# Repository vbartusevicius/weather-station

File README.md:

# AeroMet V1 — Solid-State Roof Weather & Air-Quality Station

Open-source rooftop weather and air-quality station with **no moving parts** (`Ø 96 × 235 mm`, UV-stabilised ASA):
ultrasonic wind, acoustic rain and hail, UV / sunlight / night-sky brightness, temperature, humidity, pressure, lightning,
PM1 / PM2.5 / PM10, VOC / NOx and true CO₂. It runs from `12–32 V DC`, talks Wi-Fi and RS-485, serves its own web
dashboard and appears in Home Assistant by itself.

<table>
  <tr>
    <td width="34%"></td>
    <td width="66%"></td>
  </tr>
</table>

[What it measures](#what-it-measures) · [Hardware](#hardware) · [Web UI](#web-ui) · [Build one](#build-one) ·
[Firmware](#firmware) · [Development](#development)

## What it measures

| Measurement | Sensor | Range |
| :--- | :--- | :--- |
| Wind speed & direction | 4× 40 kHz ultrasonic transducers, time of flight (STM32G431 crown) | 0–60 m/s, 0.1° |
| Rain & hail | 4 piezo discs under the lid, acoustic impacts | 0–200 mm/h, hail size |
| UV index, UV-A / UV-B, sunlight, night sky | GUVB-C21SD + GUVA-C22SD photodiodes + TSL25911 under a PTFE dome | UVI 0–16+, 0.0002–88 000 lx |
| Temperature & humidity | Sensirion SHT40 in a 5-plate radiation shield | ±0.2 °C, ±1.8 % RH |
| Pressure & thunder | Bosch BMP585 | ±0.06 hPa |
| Particulates | Plantower PMSA003I | PM1 / PM2.5 / PM10 |
| VOC & NOx | Sensirion SGP41 + Gas Index Algorithm | index 1–500 |
| CO₂ | Sensirion SCD41 (heated below −8 °C) | 400–5000 ppm |
| Lightning | AS3935 + 500 kHz ferrite antenna | 1–40 km |
| Compass, tilt, vibration | MMC5603 + LSM6DS3 | heading, mast tilt, ground vibration |

Full sensor, enclosure and board reference: **[docs/hardware.md](docs/hardware.md)**.

## Hardware

| Cutaway | Exploded | Six boards on one breakaway panel |
| :---: | :---: | :---: |
|  |  |  |
| radiation shield, probe cartridge, base bay | 13 printed parts, bayonet and threaded joints | crown, main, probe, power, dome, reflector (4-layer, 140.6 × 63.2 mm) |

<details>
<summary><b>More renders</b>: inside view, every printed part, board plots</summary>

| Inside | Base | Pagoda | Wind tunnel |
| :---: | :---: | :---: | :---: |
|  |  |  |  |
| **Crown base** | **Crown lid** | **Struts** | **Probe sleeve** |
|  |  |  |  |

Board plots (top / bottom SVG): [crown](hardware/releases/v1/crown/renders/top.svg) ·
[main](hardware/releases/v1/main/renders/top.svg) · [probe](hardware/releases/v1/probe/renders/top.svg) ·
[power](hardware/releases/v1/power/renders/top.svg) · [dome](hardware/releases/v1/dome/renders/top.svg) ·
[reflector](hardware/releases/v1/reflector/renders/top.svg) · [panel](hardware/releases/v1/panel/renders/top.svg)

</details>

## Web UI

The station serves its dashboard over Wi-Fi (no cloud, no app). Every value is computed by the firmware; the page only
displays it.

| Now | Trends |
| :---: | :---: |
|  |  |
| live readings, forecast, sun & moon, air quality, lightning | any metrics from 1 hour to 6 months, wind rose, records, CSV export |
| **Calibration** | **Setup** |
|  |  |
| station health, home calibration with household items | Wi-Fi, MQTT / Home Assistant, RS-485 monitor, firmware update |

Also: MQTT with Home Assistant auto-discovery, and an RS-485 poll / response protocol (CRC-16 frames with every
sensor) for wired loggers.

## Build one

1. **Order the boards** with assembly: ODB++ for AISLER, Gerbers + MPN BOM + CPL for PCBWay / Eurocircuits, or the
   JLCPCB files for the breakaway panel ([`hardware/releases/v1/`](hardware/releases/v1/); which file goes where:
   [docs/building.md](docs/building.md#3-ordering-the-pcbs-and-assembly)).
2. **Print the enclosure**: 8 print plates in [`enclosure/print/`](hardware/releases/v1/enclosure/print/) (MJF / SLS
   nylon or ASA), plus standard O-rings and a turned PTFE dome.
3. **Assemble and seal**: harnesses, conformal coating and sealing in **[docs/building.md](docs/building.md)**.
4. **Flash** the station once over USB, then **bring it up and calibrate** it at home:
   **[CALIBRATION.md](CALIBRATION.md)**.

Open design questions and acceptance checks: [REVIEW_CHECKLIST.md](REVIEW_CHECKLIST.md).

## Firmware

Download from **[Releases](https://github.com/vbartusevicius/weather-station/releases)**: each release carries the
firmware and the complete hardware package (`aeromet-hardware-v1.zip`: Gerbers, BOM, CPL, STL / STEP print plates,
drawings, build and calibration guides). Every commit to `main` that passes CI is released, named after its UTC commit
time (`2026.10.24.0040`); the firmware reports the same version.

| File | Use |
| :--- | :--- |
| `usb-flash-firmware.bin` | first flash of a new board over USB: `esptool.py --chip esp32c6 write_flash 0x0 usb-flash-firmware.bin` |
| `firmware.bin` | later updates from the Web UI (Setup → Firmware update); carries the crown firmware too |

The version is the UTC commit time, `yyyy.mm.dd.hhmm`. Local build: `python3 station/scripts/release_firmware.py`
→ `station/build/firmware/`.

## Development

| Folder | Contents |
| :--- | :--- |
| [`hardware/`](hardware/) | spec (`product/spec.yaml`), SKiDL circuits, KiCad layouts, simulations, release package |
| [`mechanical/`](mechanical/) | CadQuery enclosure generator and renderer |
| [`station/`](station/) | ESP32-C6 firmware (ESP-IDF), Web UI (`station/data/`), simulator, unit and Web UI tests |
| [`crown/`](crown/) | STM32G431 crown firmware (ultrasonic wind, rain, lightning) |

```bash
python3 hardware/scripts/build.py                     # everything: hardware, CAD, release, firmware, tests
docker compose --profile lint run --rm -T cpp-lint "pio test -d station -e native"   # firmware unit tests
python3 station/scripts/mock_webui_server.py          # Web UI on the simulator: http://127.0.0.1:8765
docker compose --profile lint run --rm lint check .   # lint
python3 docs/render_readme_images.py                  # refresh the README screenshots and PCB render
```

Architecture, conventions and every command: [AGENTS.md](AGENTS.md).

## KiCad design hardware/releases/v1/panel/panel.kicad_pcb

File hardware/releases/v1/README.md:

# AeroMet V1 Hardware Release Package (6 Boards on 1 Breakaway Panel + 13-Part Enclosure)

Generated by `python3 hardware/scripts/build.py` (`release.py`) from `hardware/layout/v1/` and `mechanical/`: per-board
KiCad DRC reports (`<board>/drc.json`), ODB++ (AISLER; also PCBWay / Eurocircuits), Gerber X2 + drills + IPC-D-356
netlist, a generic MPN BOM and placement file (PCBWay, Eurocircuits), JLCPCB BOM / CPL, hand-fit lists,
STEP models and renders; every JLCPCB SMT part verified pin-for-pin against its EasyEDA footprint. Which file goes to
which fab house: [`docs/building.md`](../../../docs/building.md#3-ordering-the-pcbs-and-assembly). Design status and open prototype checks:
[`REVIEW_CHECKLIST.md`](../../../REVIEW_CHECKLIST.md); commissioning: [`CALIBRATION.md`](../../../CALIBRATION.md).

| Board | Size | Layers | Thickness | Role in the Station | Folder |
| :--- | :---: | :---: | :---: | :--- | :---: |
| **Breakaway Panel (`panel`)** | **`140.6 × 63.2 mm`** | **4** | **`1.6 mm`** | **All six boards on one PCB (column packing, tabs clear of parts; order with "edge rails / fiducials added by JLCPCB"), double-sided assembly** | **`panel/`** |
| **1. `main`** | `32.0 × 52.0 mm` | 4 | `1.6 mm` | Right half of the base bay: 4-pole terminal `J1` (`12–32 V` + `RS-485 A/B`), `1.1 A` / `60 V` PTC, `SMAJ36A` TVS, `SS16` reverse-polarity diode, socketed `XIAO ESP32-C6` behind an `LM66100`, `SP3485EN` RS-485 (separate TX / RX / DE, `390 Ω` fail-safe bias, `PSM712` TVS, optional `120 Ω` `R26`), `LSM6DS3TR-C` IMU, `ADS1115` heater monitor, `AO3400A` reflector heater switch, crown control lines. Power nets `0.4 mm`. | `main/` |
| **2. `crown`** | `60 × 60 mm` (notched) | 4 | `1.6 mm` | `STM32G431RBT6` (I²C peripheral `0x2A`): 4× `UCC27524` H-bridge transducer drivers on `+12V_HEAT` with `BAV99` T/R isolation, `74HC4052` + `TLV9062` receive chain into the OPAMP1 PGA biased at VREF (PA3), piezo charge amplifier (22k / 1 nF anti-alias), `AS3935` + `MA5532-AE` on SPI1, `MMC5603NJ` compass, `XC6206` LDO, dome socket `J10`, spare `+12V_HEAT` `J11`, SWD footprint `J12`. | `crown/` |
| **3. `reflector`** | `24.0 × 24.0 mm` | 4 | `1.6 mm` | De-icing heater under the reflector cone: 4× `120 Ω` `2512` `2 W` in parallel on `+12V_HEAT` (`30 Ω`, `4.5 W` regulated), `10k` NTC `TH1`, 4-pin SMD male header `J1` to probe `J2`. | `reflector/` |
| **4. `dome`** | `Ø 15.6 mm` round | 4 | `1.6 mm` | UV / visible / NIR micro-PCB under the default flanged PTFE dome diffuser (lathe or CNC version; backup: the `Ø 20 × 2 mm` `JGS1` window in `crown_window`): `GUVB-C21SD` UV-B + `GUVA-C22SD` UV-A photodiodes, `TLV9062`, `ADS1115` (0x49), `TSL25911FN`, 4-pin B2B header `J1`. | `dome/` |
| `dome_legacy` | `Ø 13.6 mm` round | 4 | `1.6 mm` | Backup dome, same riser: `LTR-390UV-01` (discontinued), `TSL25911FN`, `GUVB-C31SM` (obsolete). Released separately (not on the panel, not in the order files). | `dome_legacy/` |
| **5. `probe`** | `14.0 × 56.0 mm` | 4 | `1.6 mm` | Vertical pagoda stem, bottom to top: `J1`, slot, `SHT40-AD1F-R2`, slot (no ground plane in its bridges), `SGP41-D-R4` + `BMP585`, `SCD41-D-R2` with the backside `0.42 W` heater and `LM2903` `−7.6 °C` thermostat, right-angle socket `J2` to the reflector. | `probe/` |
| **6. `power`** | `28.5 × 21.5 mm` | 4 | `1.6 mm` | Flat under `main`: 2× `TPS54360` (`743 kHz`) → `+5V` electronics and `+12V_HEAT` (heaters, transducer drive), `AP2112K-3.3` → `+3V3_PROBE`, 10-pin JST-SH `J1` to main `J5`. | `power/` |

Enclosure (`enclosure/`): assembled-position STL / STEP per part, `print/<plate>.stl` (8 print plates, the only files to
print), renders, and purchase drawings in `drawings/`: `ptfe_dome_lathe.svg` / `ptfe_dome_cnc.svg` (default UV / light cover:
flanged PTFE dome, lathe version from round rod or CNC hemisphere version; matching `ptfe_dome_<kind>.step` in the lathe frame for
the CNC quote) and `jgs1_window.svg` (backup window, `crown_window`
top).

Hand assembly: every board folder has `<board>_assembly.pdf`: one page per populated side (bottom mirrored, as seen
from below), every part with reference + value, a red dot on pin 1 (ICs, connectors, diodes), `[H]` on hand-fitted
parts, same value = same colour, large parts dashed (fit them last), and a value list with quantities and references.

Print process: the enclosure is designed for MJF / SLS PA12 (powder nylon, ~±0.3 mm), but **no part of it has been
printed yet** (no tested process). Design rules it follows (`mechanical/tests/test_print_rules.py`): snap beams ≤ 2.5 %
strain, hook undersides ≥ 0.3 mm above the board with a lead-in ramp, printed threads 0.30 mm flank clearance per side,
separate bodies on one plate ≥ 0.3 mm apart (reset button 0.40 mm), engraved marks ≥ 0.6 mm deep and ≥ 3 mm. Check on the
first print: clip snap force, thread fit (strut M12 + locknuts, probe sleeve M22, dome / window nuts M22), the three
bayonet joints locking, the reset button and umbrella moving freely, and the lock marks being readable.

## Parts orders for self-assembly (one complete station)

Generated by `hardware/scripts/order_parts.py` with every release (`release.py`); `hardware/tests/test_order_files.py`
fails when they differ from a fresh export. Live stock check: `python3 hardware/scripts/order_parts.py --check`.

| File | Upload to | Column mapping |
| :--- | :--- | :--- |
| `order_lcsc.csv` | lcsc.com → **BOM Tool** → Upload BOM | `LCSC Part Number` → *LCSC Part #*, `Quantity` → *Quantity*; optional `Manufacturer Part Number` → *MPN*, `Designators` → *Designator*, `Value` / `Footprint` → *Comment* / *Footprint*. Set the multiplier to 1 (one station); LCSC rounds each line up to its minimum order. |
| `order_elsewhere.csv` | by hand, per shop | electronics the LCSC store does not sell: `Mouser` / `Digi-Key` / `TME` columns (several numbers per shop separated by ` / `, the first preferred) + `Other sources`. General hardware (fasteners, O-rings, cable gland, thermal filler, coating, UV cover) and printed parts are only in `assembly_parts.csv` (column `Category`) |

`order_lcsc.csv` merges all boards (the legacy dome as `dome_legacy:ref`) into one line per LCSC number (designators `board:ref`) and adds the off-board
parts whose `Part` names an LCSC number. JLCPCB numbers the LCSC store does not stock are swapped for verified store
numbers in `hardware/product/lcsc_store.yaml` (the board BOMs keep the JLCPCB numbers). Parts the LCSC store does not sell (Sensirion SCD41 / SGP41 / SHT40, AS3935) are listed in
`order_elsewhere.csv` with a verified distributor (TME / Farnell / RS) from the `elsewhere:` section of that file. Run `--check` before ordering:
store stock changes daily, and the check lists every line that cannot be ordered as it stands.

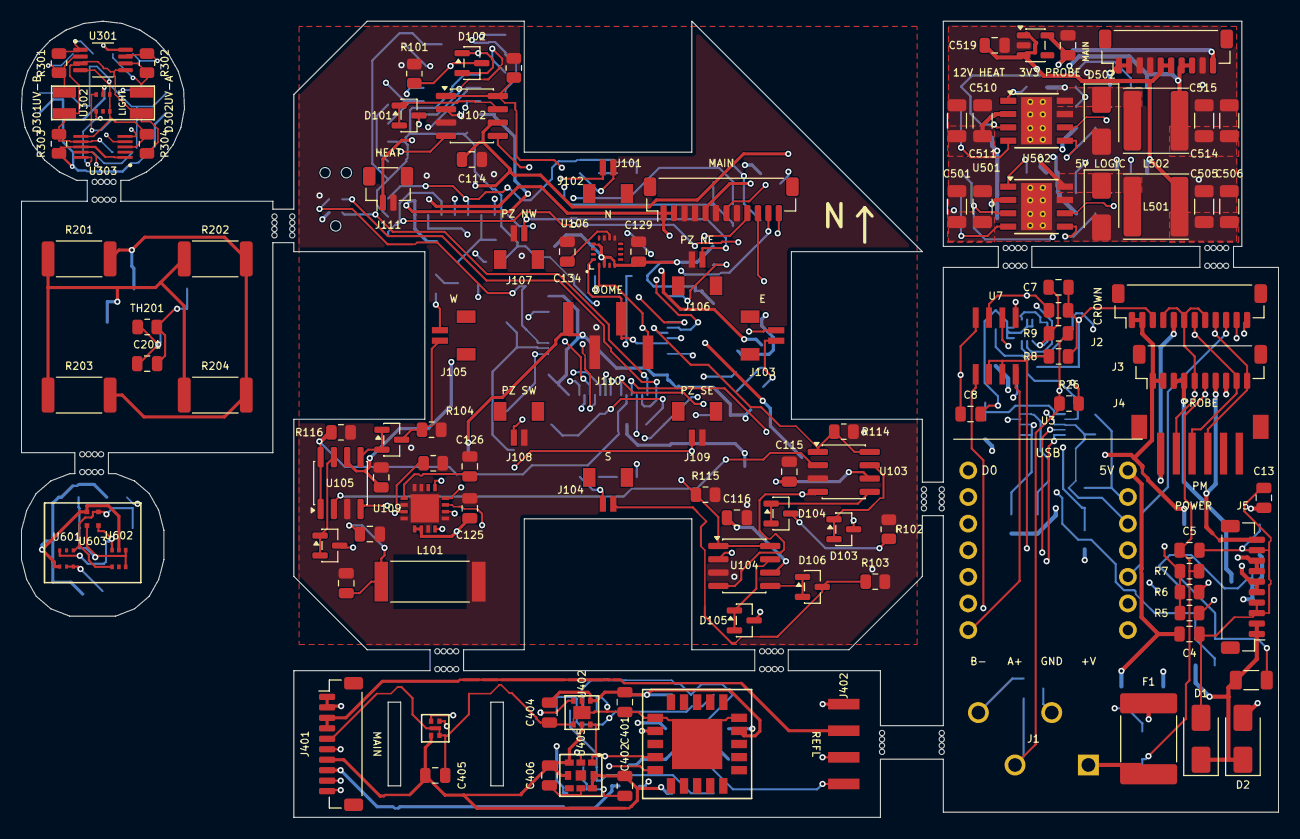
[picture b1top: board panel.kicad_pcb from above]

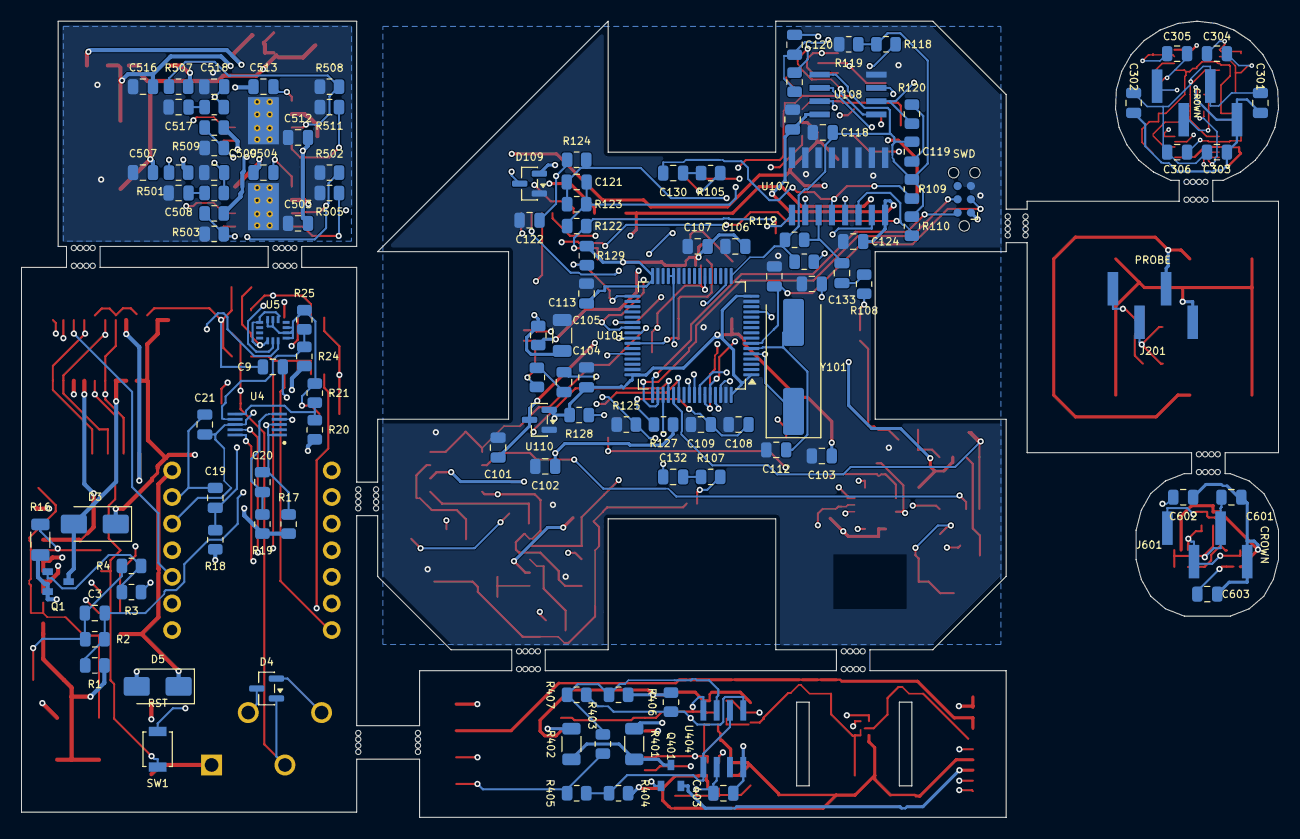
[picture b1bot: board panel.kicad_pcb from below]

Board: 4 copper layers, 120.0 x 76.0 mm, 236 parts (120 on the bottom side), 144 nets.

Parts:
C1, C501, C502, C510, C511: 2u2 100V; C_1206_3216Metric
C3, C5, C7, C8, C9, C21, C103, C104, C105, C106, C109, C110, C119, C123, C124, C129, C201, C301, C302, C303, C402, C403, C404, C405, C406, C504, C507, C513, C516, C601, C602: 100n 50V; C_0805_2012Metric
C4, C13, C102, C107, C134, C401, C520: 10u 10V; C_0805_2012Metric
C19, C20, C101, C108, C114, C115, C116, C117, C118, C125, C126, C306, C519, C603: 1u 50V; C_0805_2012Metric
C111, C112: 33p C0G 50V; C_0805_2012Metric
C113, C514, C515: 22u 25V; C_1206_3216Metric
C120: 220p C0G 50V; C_0805_2012Metric
C121, C305: 22n 50V; C_0805_2012Metric
C122: 1n 50V; C_0805_2012Metric
C127, C128: 470p C0G 50V; C_0805_2012Metric
C130, C131, C132, C133, C304: 10n 50V; C_0805_2012Metric
C503, C512: 100n 100V; C_0805_2012Metric
C505, C506: 47u 10V; C_1206_3216Metric
C508: 33n 50V; C_0805_2012Metric
C509, C518: 68p C0G 50V; C_0805_2012Metric
C517: 18n 50V; C_0805_2012Metric
D1: SMAJ36A; D_SMA
D2, D3: SS16; D_SMA
D4: PSM712; SOT-23
D5: SS14; D_SMA
D101, D102, D103, D104, D105, D106, D107, D108, D109: BAV99; SOT-23
D301: GUVB-C21SD; Genicom_COB2418
D302: GUVA-C22SD; Genicom_COB2418
D501, D502: B360A; D_SMA
F1: 1.1A; Fuse_2920_7451Metric
J1: 12-32V + RS485; TerminalBlock_Kefa_KF250-3.5-4P
J2: Crown board; JST_SH_BM12B-SRSS-TB_1x12-1MP_P1.00mm_Vertical
J3: Probe board; JST_SH_BM10B-SRSS-TB_1x10-1MP_P1.00mm_Vertical
J4: PMSA003I PM; JST_B6B-ZR-SM4-TF
J5: Power board; JST_SH_BM10B-SRSS-TB_1x10-1MP_P1.00mm_Vertical
J101: Main board; JST_SH_BM12B-SRSS-TB_1x12-1MP_P1.00mm_Vertical
J102: XD_N; JST_BM02B-SRSS-TB
J103: XD_E; JST_BM02B-SRSS-TB
J104: XD_S; JST_BM02B-SRSS-TB
J105: XD_W; JST_BM02B-SRSS-TB
J106: PIEZO_NE; JST_BM02B-SRSS-TB
J107: PIEZO_NW; JST_BM02B-SRSS-TB
J108: PIEZO_SW; JST_BM02B-SRSS-TB
J109: PIEZO_SE; JST_BM02B-SRSS-TB
J110: DOME_SOCKET; HX_PZ2.54-1x4P-SMD
J111: AUX 12V_HEAT; JST_SH_BM02B-SRSS-TB_1x02-1MP_P1.00mm_Vertical
J112: SWD; Tag-Connect_TC2030-IDC-NL_2x03_P1.27mm_Vertical
J201: Probe T-Header SMD; HX_PZ2.54-1x4P-SMD
J301, J601: CROWN_RISER; HX_PZ2.54-1x4P-SMD
J401, J501: Main board; JST_SH_BM10B-SRSS-TB_1x10-1MP_P1.00mm_Vertical
J402: Reflector T-Socket SMD; HX_PM2.54-1x4P-RA-SMD
L101: 100uH; AS3935_Antenna_MA5532_SDTR1103
L501: 8.2uH; L_Sunlord_SWPA6045S
L502: 22uH; L_Sunlord_SWPA6045S
MOUSE_BITES: DNP
Q1, Q401: AO3400A; AOS_AO3400A_SOT-23
R1, R4, R303: 100k; R_0805_2012Metric
R2, R7, R8, R21, R24, R25, R118, R119, R125, R126, R128, R129, R304, R403, R404, R406, R510: 10k; R_0805_2012Metric
R3, R101, R102, R103, R104: 330R; R_0805_2012Metric
R5, R6: 2k2; R_0805_2012Metric
R9, R10: 390R; R_0805_2012Metric
R16: 0R1; R_1206_3216Metric
R17: 1R; R_0805_2012Metric
R18, R19, R120, R122: 1k; R_0805_2012Metric
R20: 30k; R_0805_2012Metric
R26: 120R; R_0805_2012Metric
R105, R106, R107, R108: 47k; R_0805_2012Metric
R109, R110, R111, R112: 1M; R_0805_2012Metric
R113, R114, R115, R116: 4k7; R_0805_2012Metric
R117, R127: 10R; R_0805_2012Metric
R121: 6k8; R_0805_2012Metric
R123, R302: 4M7; R_0805_2012Metric
R124: 22k; R_0805_2012Metric
R201, R202, R203, R204: 120R; R_2512_6332Metric
R301: 10M; R_0805_2012Metric
R401, R402: 680R; R_1206_3216Metric
R405: 51k; R_0805_2012Metric
R407: 470k; R_0805_2012Metric
R501, R507: 511k; R_0805_2012Metric
R502, R508: 82k5; R_0805_2012Metric
R503: 53k6; R_0805_2012Metric
R504: 10k2; R_0805_2012Metric
R505, R511: 130k; R_0805_2012Metric
R506, R512: 6k49; R_0805_2012Metric
R509: 140k; R_0805_2012Metric
SW1: SERVICE; SW_SPST_B3U-1000P
TH201, TH401: 10k NTC; R_0805_2012Metric
U3: XIAO ESP32C6; XIAO_ESP32C6_Header
U4, U303: ADS1115IDGSR; TI_ADS1115_VSSOP-10
U5: LSM6DS3TR-C; ST_LSM6DS3TR-C_LGA-14
U7: SP3485EN-L/TR; ON_LM393DR2G_SOIC-8
U101: STM32G431RBT6; LQFP-64_10x10mm_P0.5mm
U102, U103, U104, U105: UCC27524ADR; SOIC-8_3.9x4.9mm_P1.27mm
U106: MMC5983MA; MEMSIC_MMC5983MA_LGA-16
U107: 74HC4052D; TI_CD4052BM96_SOIC-16
U108: TLV9062IDR; TI_TLV9062IDR_SOIC-8
U109: AS3935-BQFT; ScioSense_AS3935_QFN-16
U110: XC6206P332MR; SOT-23
U301: TLV9062IDGKR; TI_TLV9062_VSSOP-8
U302, U602: TSL25911FN; AMS_TSL25911FN
U401: SCD41-D-R2; Sensirion_SCD41_LGA-20
U402: SGP41-D-R4; Sensirion_SGP41_DFN-6
U403: SHT40-AD1F-R2; Sensirion_SHT45_DFN-4
U404: LM2903DR2G; ON_LM393DR2G_SOIC-8
U405: BMP585; Bosch_BMP585_LGA-9
U501, U502: TPS54360DDAR; TI_SO-PowerPAD-8_ThermalVias
U503: AP2112K-3.3; SOT-23-5
U601: LTR-390UV-01; LiteOn_LTR-390UV-01
U603: GUVB-C31SM; GenUV_GUVB-C31SM
Y101: 8MHz; Crystal_SMD_HC49-SD

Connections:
+3V3: C7.1, C8.1, C9.1, C21.1, R5.1, R6.1, R7.1, R9.1, U3.12, U4.8, U5.5, U5.8, U5.12, U7.8
+3V3_PROBE: J3.7, J5.10
+5V: C13.1, D5.2, J2.5, J4.1, J5.5, J5.6, R24.1
+5V_XIAO: C4.1, D5.1, U3.14
+12V_HEAT: D3.1, J2.1, J2.2, J3.1, J3.2, J5.7, J5.8, R20.1
CO2_HEAT_RTN: J3.8, R17.1, R19.1
CROWN_+3V3: C102.1, C103.1, C104.1, C105.1, C106.1, C107.1, C123.1, C124.1, C125.1, C129.1, D109.2, J110.1, J112.1, R127.1, R128.2, R129.2, U101.1, U101.16, U101.32, U101.48, U101.64, U106.2, U106.4, U106.13, U107.16, U108.8, U109.5, U109.6, U110.2
CROWN_+3V3A: C108.1, C109.1, R118.1, R127.2, U101.28, U101.29
CROWN_+5V: C101.1, J101.5, U110.3
CROWN_+12V_HEAT: J101.1, J101.2, J111.1, R117.1
CROWN_AS_ACG: C126.1, U109.1
CROWN_AS_CS: U101.51, U109.8
CROWN_AS_INP: C127.1, C128.1, L101.1, R126.1, U109.3
CROWN_AS_IRQ: U101.62, U109.10
CROWN_AS_MISO: U101.57, U109.12
CROWN_AS_MOSI: U101.58, U109.13
CROWN_AS_SCK: U101.56, U109.11
CROWN_BL_PA10: R128.1, U101.44
CROWN_BL_PB12: R129.1, U101.33
CROWN_BOOT0: J2.12, U3.3
CROWN_CROWN_BOOT0: J101.12, R125.1, U101.61
CROWN_CROWN_IRQ: J101.10, U101.54
CROWN_CROWN_NRST: C110.1, J101.11, J112.3, U101.7
CROWN_GND: C101.2, C102.2, C103.2, C104.2, C105.2, C106.2, C107.2, C108.2, C109.2, C110.2, C111.2, C112.2, C113.2, C114.2, C115.2, C116.2, C117.2, C118.2, C122.2, C123.2, C124.2, C125.2, C126.2, C127.2, C128.2, C129.2, C134.2, D109.1, J101.3, J101.4, J101.6, J101.8, J106.2, J107.2, J108.2, J109.2, J110.2, J111.2, J112.5, L101.2, R101.2, R102.2, R103.2, R104.2, R113.2, R114.2, R115.2, R116.2, R119.2, R125.2, R126.2, U101.15, U101.27, U101.31, U101.47, U101.63, U102.3, U103.3, U104.3, U105.3, U106.9, U106.11, U107.1, U107.2, U107.3, U107.4, U107.5, U107.6, U107.7, U107.8, U108.4, U109.2, U109.4, U109.7, U109.9, U109.15, U109.16, U109.17, U110.1
CROWN_I2C_SCL: J101.9, J110.4, U101.22, U106.1
CROWN_I2C_SDA: J101.7, J110.3, U101.42, U106.16
CROWN_IRQ: J2.10, U3.10
CROWN_MAG_CAP: C134.1, U106.10
CROWN_MUX_S0: U101.59, U107.10
CROWN_MUX_S1: U101.60, U107.9
CROWN_NRST: J2.11, U3.11
CROWN_PIEZO_IN: D109.3, J106.1, J107.1, J108.1, J109.1, R122.1
CROWN_PIEZO_INV: C121.1, R122.2, R123.1, U108.6
CROWN_PIEZO_OUT: C121.2, R123.2, R124.1, U108.7
CROWN_RAIN_ADC: C122.1, R124.2, U101.18
CROWN_SWCLK: J112.4, U101.50
CROWN_SWDIO: J112.2, U101.49
CROWN_TX_N: U101.52, U102.4, U103.4, U104.4, U105.4
CROWN_TX_P: U101.38, U102.2, U103.2, U104.2, U105.2
CROWN_US_AMP_FB: C120.1, R120.1, R121.1, U108.2
CROWN_US_AMP_G: C119.1, R120.2
CROWN_US_AMP_OUT: C120.2, R121.2, U101.13, U108.1
CROWN_US_RX_MUX: U107.13, U108.3
CROWN_US_VREF: C118.1, C119.2, R109.2, R110.2, R111.2, R112.2, R118.2, R119.1, U101.17, U108.5
CROWN_VDRV: C113.1, C114.1, C115.1, C116.1, C117.1, R117.2, U102.6, U103.6, U104.6, U105.6
CROWN_XD_EN_E: R114.1, U101.40, U103.1, U103.8
CROWN_XD_EN_N: R113.1, U101.39, U102.1, U102.8
CROWN_XD_EN_S: R115.1, U101.41, U104.1, U104.8
CROWN_XD_EN_W: R116.1, U101.53, U105.1, U105.8
CROWN_XD_E_A: D103.3, J103.1, R106.1
CROWN_XD_E_B: D104.3, J103.2, R102.1
CROWN_XD_E_OUT_A: D103.1, D103.2, U103.7
CROWN_XD_E_OUT_B: D104.1, D104.2, U103.5
CROWN_XD_E_RX: C131.2, R110.1, U107.14
CROWN_XD_E_RXC: C131.1, R106.2
CROWN_XD_N_A: D101.3, J102.1, R105.1
CROWN_XD_N_B: D102.3, J102.2, R101.1
CROWN_XD_N_OUT_A: D101.1, D101.2, U102.7
CROWN_XD_N_OUT_B: D102.1, D102.2, U102.5
CROWN_XD_N_RX: C130.2, R109.1, U107.12
CROWN_XD_N_RXC: C130.1, R105.2
CROWN_XD_S_A: D105.3, J104.1, R107.1
CROWN_XD_S_B: D106.3, J104.2, R103.1
CROWN_XD_S_OUT_A: D105.1, D105.2, U104.7
CROWN_XD_S_OUT_B: D106.1, D106.2, U104.5
CROWN_XD_S_RX: C132.2, R111.1, U107.15
CROWN_XD_S_RXC: C132.1, R107.2
CROWN_XD_W_A: D107.3, J105.1, R108.1
CROWN_XD_W_B: D108.3, J105.2, R104.1
CROWN_XD_W_OUT_A: D107.1, D107.2, U105.7
CROWN_XD_W_OUT_B: D108.1, D108.2, U105.5
CROWN_XD_W_RX: C133.2, R112.1, U107.11
CROWN_XD_W_RXC: C133.1, R108.2
CROWN_XTAL_IN: C111.1, U101.5, Y101.1
CROWN_XTAL_OUT: C112.1, U101.6, Y101.2
DOME_+3V3: C301.1, C302.1, C303.1, J301.1, R303.1, U301.8, U302.5, U303.1, U303.8
DOME_GND: C301.2, C302.2, C303.2, C306.2, J301.2, R304.2, U301.4, U302.3, U302.4, U303.3, U303.6
DOME_I2C_SCL: J301.4, U302.1, U303.10
DOME_I2C_SDA: J301.3, U302.6, U303.9
DOME_LEGACY_+3V3: C601.1, C602.1, C603.1, J601.1, U601.1, U602.5, U603.4
DOME_LEGACY_GND: C601.2, C602.2, C603.2, J601.2, U601.2, U601.3, U602.3, U602.4, U603.1
DOME_LEGACY_I2C_SCL: J601.4, U601.4, U602.1, U603.3
DOME_LEGACY_I2C_SDA: J601.3, U601.6, U602.6, U603.2
DOME_UVA_IN: C305.1, D302.2, R302.1, U301.6
DOME_UVA_OUT: C305.2, R302.2, U301.7, U303.5
DOME_UVB_IN: C304.1, D301.2, R301.1, U301.2
DOME_UVB_OUT: C304.2, R301.2, U301.1, U303.4
DOME_UV_VB: C306.1, D301.1, D302.1, R303.2, R304.1, U301.3, U301.5, U303.7
GND: C1.2, C3.2, C4.2, C5.2, C7.2, C8.2, C9.2, C13.2, C19.2, C20.2, C21.2, D1.2, D4.3, J1.2, J2.3, J2.4, J2.6, J2.8, J3.5, J4.2, J5.3, J5.4, J5.9, R2.2, R4.2, R8.2, R10.2, R16.2, R17.2, R21.2, R25.2, SW1.2, U3.13, U4.1, U4.3, U5.1, U5.2, U5.3, U5.6, U5.7, U7.5
HEAT_GATE: Q1.1, R3.2, R4.1
HEAT_PWM: R3.1, U3.4
HEAT_SENSE: Q1.2, R16.1, R18.1
HEAT_SW: D3.2, J3.3, J3.4, Q1.3
I2C_SCL: J2.9, J3.10, J4.4, R6.2, U3.6, U4.10, U5.13
I2C_SDA: J2.7, J3.9, J4.3, R5.2, U3.5, U4.9, U5.14
MON_5V: R20.2, R21.1, U4.6
MON_5V_LOGIC: R24.2, R25.1, U4.7
MON_PROBE: C20.1, R19.2, U4.5
MON_REFL: C19.1, R18.2, U4.4
NTC_SENSE: C5.1, J3.6, R7.2, SW1.1, U3.2
POWER_+3V3_PROBE: C520.1, J501.10, U503.5
POWER_+5V: C505.1, C506.1, C507.1, C519.1, J501.5, J501.6, L501.2, R503.1, U503.1, U503.3
POWER_+12V_HEAT: C514.1, C515.1, C516.1, J501.7, J501.8, L502.2, R509.1
POWER_GND: C501.2, C502.2, C503.2, C505.2, C506.2, C507.2, C508.2, C509.2, C510.2, C511.2, C512.2, C514.2, C515.2, C516.2, C517.2, C518.2, C519.2, C520.2, D501.2, D502.2, J501.3, J501.4, J501.9, R502.2, R504.2, R505.2, R508.2, R510.2, R511.2, U501.7, U501.9, U502.7, U502.9, U503.2
POWER_HEAT_BST: C513.1, U502.1
POWER_HEAT_CC: C517.1, R512.2
POWER_HEAT_COMP: C518.1, R512.1, U502.6
POWER_HEAT_EN: R507.2, R508.1, U502.3
POWER_HEAT_FB: R509.2, R510.1, U502.5
POWER_HEAT_RT: R511.1, U502.4
POWER_HEAT_SW: C513.2, D502.1, L502.1, U502.8
POWER_LOGIC_BST: C504.1, U501.1
POWER_LOGIC_CC: C508.1, R506.2
POWER_LOGIC_COMP: C509.1, R506.1, U501.6
POWER_LOGIC_EN: R501.2, R502.1, U501.3
POWER_LOGIC_FB: R503.2, R504.1, U501.5
POWER_LOGIC_RT: R505.1, U501.4
POWER_LOGIC_SW: C504.2, D501.1, L501.1, U501.8
POWER_VIN_PROT: C501.1, C502.1, C503.1, C510.1, C511.1, C512.1, J501.1, J501.2, R501.1, R507.1, U501.2, U502.2
PROBE_+3V3_PROBE: C401.1, C402.1, C404.1, C405.1, C406.1, J401.7, R403.1, R404.1, R406.1, U401.7, U401.19, U402.1, U402.5, U403.3, U405.3, U405.4, U405.7, U405.8
PROBE_+12V_HEAT: C403.1, J401.1, J401.2, J402.1, R401.1, R402.1, U404.8
PROBE_CO2_GATE: Q401.1, R406.2, R407.1, U404.1
PROBE_CO2_HEAT_RTN: J401.8, Q401.2
PROBE_CO2_HEAT_SW: Q401.3, R401.2, R402.2
PROBE_CO2_NTC: R403.2, R407.2, TH401.1, U404.3
PROBE_CO2_VSET: R404.2, R405.1, U404.2, U404.5
PROBE_GND: C401.2, C402.2, C403.2, C404.2, C405.2, C406.2, J401.5, J402.4, R405.2, TH401.2, U401.6, U401.20, U401.21, U402.2, U402.4, U402.7, U403.4, U403.5, U404.4, U404.6, U405.6
PROBE_HEAT_SW: J401.3, J401.4, J402.2
PROBE_I2C_SCL: J401.10, U401.9, U402.6, U403.2, U405.1
PROBE_I2C_SDA: J401.9, U401.10, U402.3, U403.1, U405.2
PROBE_NTC_SENSE: J401.6, J402.3
REFLECTOR_+12V_HEAT: J201.1, R201.1, R202.1, R203.1, R204.1
REFLECTOR_GND: C201.2, J201.4, TH201.2
REFLECTOR_HEAT_SW: J201.2, R201.2, R202.2, R203.2, R204.2
REFLECTOR_NTC_SENSE: C201.1, J201.3, TH201.1
RS485_A: D4.1, J1.3, R9.2, R26.1, U7.6
RS485_B: D4.2, J1.4, R10.1, R26.2, U7.7
RS485_DE: R8.1, U3.9, U7.2, U7.3
RS485_RX: U3.8, U7.1
RS485_TX: U3.7, U7.4
VIN_ADC: C3.1, R1.2, R2.1, U3.1
VIN_FUSED: D2.2, F1.2
VIN_PROT: C1.1, D1.1, D2.1, J5.1, J5.2, R1.1
VIN_RAW: F1.1, J1.1

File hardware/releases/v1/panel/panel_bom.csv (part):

Line,Qty,Designators,Value,Package,Type,Manufacturer,MPN,LCSC,Assembly
1,5,"C1,C501,C502,C510,C511",2u2 100V,C_1206_3216Metric,SMD,Samsung,CL31B225KCHSNNE,C170101,machine
2,14,"C101,C108,C114,C115,C116,C117,C118,C125,C126,C19,C20,C306,C519,C603",1u 50V,C_0805_2012Metric,SMD,Samsung,CL21B105KBFNNNE,C28323,machine
3,7,"C102,C107,C13,C134,C4,C401,C520",10u 10V,C_0805_2012Metric,SMD,Samsung,CL21A106KPFNNNE,C17024,machine
4,31,"C103,C104,C105,C106,C109,C110,C119,C123,C124,C129,C201,C21,C3,C301,C302,C303,C402,C403,C404,C405,C406,C5,C504,C507,C513,C516,C601,C602,C7,C8,C9",100n 50V,C_0805_2012Metric,SMD,YAGEO,CC0805KRX7R9BB104,C49678,machine
5,2,"C111,C112",33p C0G 50V,C_0805_2012Metric,SMD,YAGEO,CC0805JRNPO9BN330,C107115,machine
6,3,"C113,C514,C515",22u 25V,C_1206_3216Metric,SMD,Samsung,CL31A226KAHNNNE,C12891,machine
7,1,C120,220p C0G 50V,C_0805_2012Metric,SMD,YAGEO,CC0805JRNPO9BN221,C107112,machine
8,2,"C121,C305",22n 50V,C_0805_2012Metric,SMD,YAGEO,CC0805KRX7R9BB223,C107147,machine
9,1,C122,1n 50V,C_0805_2012Metric,SMD,YAGEO,CC0805KRX7R9BB102,C94121,machine
10,2,"C127,C128",470p C0G 50V,C_0805_2012Metric,SMD,YAGEO,CC0805JRNPO9BN471,C62771,machine
11,5,"C130,C131,C132,C133,C304",10n 50V,C_0805_2012Metric,SMD,YAGEO,CC0805KRX7R9BB103,C83170,machine
12,2,"C503,C512",100n 100V,C_0805_2012Metric,SMD,YAGEO,CC0805KKX7R0BB104,C106243,machine
13,2,"C505,C506",47u 10V,C_1206_3216Metric,SMD,Samsung,CL31A476MPHNNNE,C96123,machine
14,1,C508,33n 50V,C_0805_2012Metric,SMD,YAGEO,CC0805KRX7R9BB333,C107150,machine
15,2,"C509,C518",68p C0G 50V,C_0805_2012Metric,SMD,YAGEO,CC0805JRNPO9BN680,C107120,machine
16,1,C517,18n 50V,C_0805_2012Metric,SMD,YAGEO,CC0805JRX7R9BB183,C520032,machine
17,1,D1,SMAJ36A,D_SMA,SMD,MDD,SMAJ36A,C113967,machine
18,9,"D101,D102,D103,D104,D105,D106,D107,D108,D109",BAV99,SOT-23,SMD,Nexperia,"BAV99,215",C2500,machine
19,2,"D2,D3",SS16,D_SMA,SMD,MDD,SS16,C2481,machine
20,1,D301,GUVB-C21SD,Genicom_COB2418,SMD,Genicom,GUVB-C21SD,,hand-fit (not stocked by JLCPCB)
21,1,D302,GUVA-C22SD,Genicom_COB2418,SMD,Genicom,GUVA-C22SD,,hand-fit (not stocked by JLCPCB)
22,1,D4,PSM712,SOT-23,SMD,Protek,PSM712-LF-T7,C32677,machine
23,1,D5,SS14,D_SMA,SMD,MDD,SS14,C2480,machine
24,2,"D501,D502",B360A,D_SMA,SMD,Diodes Inc,B360A-13-F,C94193,machine
25,1,F1,1.1A,Fuse_2920_7451Metric,SMD,Littelfuse,2920L110/60V,C49318488,machine
26,1,J1,12-32V + RS485,TerminalBlock_Kefa_KF250-3.5-4P,THT,Cixi Kefa Elec,KF250-3.5-4P-1,C475156,machine
27,1,J101,Main board,JST_SH_BM12B-SRSS-TB_1x12-1MP_P1.00mm_Vertical,SMD,JST,BM12B-SRSS-TB(LF)(SN),C160398,machine
28,1,J102,XD_N,JST_BM02B-SRSS-TB,SMD,JST,BM02B-SRSS-TB(LF)(SN),C160388,machine
29,1,J103,XD_E,JST_BM02B-SRSS-TB,SMD,JST,BM02B-SRSS-TB(LF)(SN),C160388,machine
30,1,J104,XD_S,JST_BM02B-SRSS-TB,SMD,JST,BM02B-SRSS-TB(LF)(SN),C160388,machine
31,1,J105,XD_W,JST_BM02B-SRSS-TB,SMD,JST,BM02B-SRSS-TB(LF)(SN),C160388,machine
32,1,J106,PIEZO_NE,JST_BM02B-SRSS-TB,SMD,JST,BM02B-SRSS-TB(LF)(SN),C160388,machine
33,1,J107,PIEZO_NW,JST_BM02B-SRSS-TB,SMD,JST,BM02B-SRSS-TB(LF)(SN),C160388,machine
34,1,J108,PIEZO_SW,JST_BM02B-SRSS-TB,SMD,JST,BM02B-SRSS-TB(LF)(SN),C160388,machine
35,1,J109,PIEZO_SE,JST_BM02B-SRSS-TB,SMD,JST,BM02B-SRSS-TB(LF)(SN),C160388,machine
36,1,J110,DOME_SOCKET,HX_PZ2.54-1x4P-SMD,SMD,HCTL,HX PM2.54-1x4P TP-YQ,C42379197,machine
37,1,J111,AUX 12V_HEAT,JST_SH_BM02B-SRSS-TB_1x02-1MP_P1.00mm_Vertical,SMD,JST,BM02B-SRSS-TB(LF)(SN),C160388,machine
38,1,J2,Crown board,JST_SH_BM12B-SRSS-TB_1x12-1MP_P1.00mm_Vertical,SMD,JST,BM12B-SRSS-TB(LF)(SN),C160398,machine
39,1,J201,Probe T-Header SMD,HX_PZ2.54-1x4P-SMD,SMD,HANBO,HX PZ2.54-1x4P TP-YQ,C41417361,machine
40,1,J3,Probe board,JST_SH_BM10B-SRSS-TB_1x10-1MP_P1.00mm_Vertical,SMD,JST,BM10B-SRSS-TB(LF)(SN),C160396,machine
41,2,"J301,J601",CROWN_RISER,HX_PZ2.54-1x4P-SMD,SMD,HCTL,HX PZ2.54-1x4P TP-YQ,C41417361,machine
42,1,J4,PMSA003I PM,JST_B6B-ZR-SM4-TF,SMD,JST,B6B-ZR-SM4-TF(LF)(SN),C471473,machine
43,2,"J401,J501",Main board,JST_SH_BM10B-SRSS-TB_1x10-1MP_P1.00mm_Vertical,SMD,JST,BM10B-SRSS-TB(LF)(SN),C160396,machine
44,1,J402,Reflector T-Socket SMD,HX_PM2.54-1x4P-RA-SMD,SMD,HANBO,HX PM2.54-1x4P WT,C46061768,machine
45,1,J5,Power board,JST_SH_BM10B-SRSS-TB_1x10-1MP_P1.00mm_Vertical,SMD,JST,BM10B-SRSS-TB(LF)(SN),C160396,machine
46,1,L101,100uH,AS3935_Antenna_MA5532_SDTR1103,SMD,Coilcraft,MA5532-AE,,hand-fit (not stocked by JLCPCB)
47,1,L501,8.2uH,L_Sunlord_SWPA6045S,SMD,APV,ANR6045T8R2M,C7427168,machine
48,1,L502,22uH,L_Sunlord_SWPA6045S,SMD,Bourns,SRN6045TA-220M,C2044314,machine
49,2,"Q1,Q401",AO3400A,AOS_AO3400A_SOT-23,SMD,Alpha & Omega Semicon,AO3400A,C20917,machine
50,3,"R1,R303,R4",100k,R_0805_2012Metric,SMD,UNI-ROYAL,0805W8F1003T5E,C149504,machine
51,2,"R10,R9",390R,R_0805_2012Metric,SMD,UNI-ROYAL,0805W8F3900T5E,C17655,machine
52,5,"R101,R102,R103,R104,R3",330R,R_0805_2012Metric,SMD,UNI-ROYAL,0805W8F3300T5E,C17630,machine
53,4,"R105,R106,R107,R108",47k,R_0805_2012Metric,SMD,UNI-ROYAL,0805W8F4702T5E,C17713,machine
54,4,"R109,R110,R111,R112",1M,R_0805_2012Metric,SMD,UNI-ROYAL,0805W8F1004T5E,C17514,machine
55,4,"R113,R114,R115,R116",4k7,R_0805_2012Metric,SMD,UNI-ROYAL,0805W8F4701T5E,C17673,machine
56,2,"R117,R127",10R,R_0805_2012Metric,SMD,UNI-ROYAL,0805W8F100JT5E,C17415,machine
57,17,"R118,R119,R125,R126,R128,R129,R2,R21,R24,R25,R304,R403,R404,R406,R510,R7,R8",10k,R_0805_2012Metric,SMD,UNI-ROYAL,0805W8F1002T5E,C17414,machine
58,4,"R120,R122,R18,R19",1k,R_0805_2012Metric,SMD,UNI-ROYAL,0805W8F1001T5E,C17513,machine
59,1,R121,6k8,R_0805_2012Metric,SMD,UNI-ROYAL,0805W8F6801T5E,C17772,machine
60,2,"R123,R302",4M7,R_0805_2012Metric,SMD,UNI-ROYAL,0805W8F4704T5E,C17674,machine
61,1,R124,22k,R_0805_2012Metric,SMD,UNI-ROYAL,0805W8F2202T5E,C17560,machine
62,1,R16,0R1,R_1206_3216Metric,SMD,UNI-ROYAL,1206W4F100LT5E,C25334,machine
63,1,R17,1R,R_0805_2012Metric,SMD,UNI-ROYAL,0805W8F100KT5E,C25271,machine
64,1,R20,30k,R_0805_2012Metric,SMD,UNI-ROYAL,0805W8F3002T5E,C17621,machine
65,4,"R201,R202,R203,R204",120R,R_2512_6332Metric,SMD,YAGEO,RC2512FK-7W120RL,C7276687,machine
66,1,R26,120R,R_0805_2012Metric,SMD,UNI-ROYAL,0805W8F1200T5E,C17437,hand-fit (not stocked by JLCPCB)
67,1,R301,10M,R_0805_2012Metric,SMD,UNI-ROYAL,0805W8F1005T5E,C26108,machine
68,2,"R401,R402",680R,R_1206_3216Metric,SMD,FOJAN,FRP1206F6800TS,C48533685,machine
69,1,R405,51k,R_0805_2012Metric,SMD,UNI-ROYAL,0805W8F5102T5E,C17737,machine
70,1,R407,470k,R_0805_2012Metric,SMD,UNI-ROYAL,0805W8F4703T5E,C17709,machine
71,2,"R5,R6",2k2,R_0805_2012Metric,SMD,UNI-ROYAL,0805W8F2201T5E,C17520,machine
72,2,"R501,R507",511k,R_0805_2012Metric,SMD,UNI-ROYAL,0805W8F5113T5E,C17735,machine
73,2,"R502,R508",82k5,R_0805_2012Metric,SMD,YAGEO,RC0805FR-0782K5L,C276314,machine
74,1,R503,53k6,R_0805_2012Metric,SMD,UNI-ROYAL,0805W8F5362T5E,C21398,machine
75,1,R504,10k2,R_0805_2012Metric,SMD,UNI-ROYAL,0805W8F1022T5E,C17402,machine
76,2,"R505,R511",130k,R_0805_2012Metric,SMD,UNI-ROYAL,0805W8F1303T5E,C17450,machine
77,2,"R506,R512",6k49,R_0805_2012Metric,SMD,UNI-ROYAL,0805W8F6491T5E,C17769,machine
78,1,R509,140k,R_0805_2012Metric,SMD,UNI-ROYAL,0805W8F1403T5E,C17460,machine
79,1,SW1,SERVICE,SW_SPST_B3U-1000P,SMD,Omron,B3U-1000P,C231329,machine
80,2,"TH201,TH401",10k NTC,R_0805_2012Metric,SMD,R+O,HNTC0805-103F3950FB,C49247662,machine
81,1,U101,STM32G431RBT6,LQFP-64_10x10mm_P0.5mm,SMD,STMicroelectronics,STM32G431RBT6,C431633,machine
82,4,"U102,U103,U104,U105",UCC27524ADR,SOIC-8_3.9x4.9mm_P1.27mm,SMD,Texas Instruments,UCC27524ADR,C185857,machine
83,1,U106,MMC5983MA,MEMSIC_MMC5983MA_LGA-16,SMD,MEMSIC,MMC5983MA,C404329,machine
84,1,U107,74HC4052D,TI_CD4052BM96_SOIC-16,SMD,Nexperia,"74HC4052D,653",C11350,machine
85,1,U108,TLV9062IDR,TI_TLV9062IDR_SOIC-8,SMD,Texas Instruments,TLV9062IDR,C398355,machine
86,1,U109,AS3935-BQFT,ScioSense_AS3935_QFN-16,SMD,ScioSense,AS3935-BQFT,,hand-fit (not stocked by JLCPCB)
87,1,U110,XC6206P332MR,SOT-23,SMD,Torex,XC6206P332MR-G,C5446,machine
88,1,U3,XIAO ESP32C6,XIAO_ESP32C6_Header,THT,Seeed Studio,102010636,,hand-fit (not stocked by JLCPCB)
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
